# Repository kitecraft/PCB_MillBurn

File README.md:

<div align="center">
  
  <h1>PCB_MillBurn</h1>
  <p>
    <b>Turn your Gerber files into a circuit board.</b><br>
    G-code for the mill. SVG for the laser. One app, one board, no guesswork.
  </p>
  <p>

  </p>
  <p>
    <a href="https://github.com/kitecraft/PCB_MillBurn/releases/latest"><b>Download</b></a> ·
    <a href="#quick-start">Quick start</a> ·
    <a href="#status">What has been proven on metal</a> ·
    <a href="Documentation/README.md">Design docs</a>
  </p>
</div>

---

<sub>A 66-up panel — 11,414 objects, 198 copper islands — with the emitted isolation and cut-out programs drawn back over the copper they were made from.</sub>

---

## What it does

Drop a folder of Gerbers on the window. The board appears. Tell each layer what it should become.
Press Export.

- **Mill it.** Isolation routing, drilling one file per bit, slots and oversized holes routed with an
  end mill, soldermask relief, cut-out with tabs — and, if you like, the copper-clad cut to size first
  so its edges become the datum for everything after.
- **Burn it.** Laser-ready SVG at true 1:1 millimetres, for LightBurn or Inkscape.
- **Or both.** Make the copper with the laser, then drill and cut out on the mill. Same board, same
  origin, same export — and a drill alignment test that lands the holes in the pads.

Every file is one layer. Every file in an export shares one work zero — the board's lower-left
corner, or the stock's. Nothing is written until you have seen a list of exactly what is about to be
written, and every export comes with an HTML page saying what to run, in what order, with which bit.

**It writes files. It does not drive machines.** No serial port, no jogging, no streaming — gSender,
UGS, Candle, LightBurn and LinuxCNC already do that well.

---

## Quick start

1. **Get it.** Download the latest [release](https://github.com/kitecraft/PCB_MillBurn/releases/latest)
   for Windows or Linux, unpack it anywhere, and run `MillBurn` (`MillBurn.exe` on Windows) — the
   folder holds it, `millburn-cli` and the help, nothing else. It is self-contained — you do not
   need .NET installed. (On a fresh Debian or Ubuntu you may need `sudo apt install libfontconfig1`.)
2. **Open a board.** Drag your Gerber export folder onto the window, or `File ▸ Import Gerber
   folder…`. Drill files come along with it. Exporting from KiCad? The
   [export guide](Help/guides/kicad-export.html) lists the settings that work best.
3. **Set the board thickness** in Project info. Everything that cuts through uses it, and it is saved
   with the project. The top of that panel says which folder the Gerbers were read from, in full —
   worth a glance when two of your folders share a name.
4. **Tell each layer what it becomes.** Open a layer row and pick **G-code (mill)**, **SVG
   (laser)**, or **Not exported**. The pill on the collapsed row shows what you chose.
5. **Press Preview** (F5). The programs are drawn back over your board.
6. **Press Export…** (Ctrl+E). Read the list. Choose a folder. Open `YourBoard.project.html` beside
   the files for the run order — and, at its foot, the CLI commands that would write that same
   folder again.

Press **F1** at any point. The help, the questions-and-answers page and the step-by-step guides ship
with the app and work with no network, which is the condition a workshop is usually in.

---

## How to

### Mill a board

| Layer | Set it to | You get |
|---|---|---|
| Top / bottom copper | G-code | Isolation routing around every trace and pad |
| Plated / non-plated holes | G-code | One drilling file per bit, a `.slots.nc` for slots and holes too big to drill, and a page listing them in the suggested order |
| Board outline | G-code | Cut-out with tabs, in depth passes |
| Soldermask | G-code | Mask relief — mills the mask off the pads only |
| *Project info ▸ Build on stock* | — | A `.stock.nc` that cuts the copper-clad to size first; its corner becomes work zero for every file |

Run order on the machine: **stock (if you use it), isolate, drill, cut out.** Between drilling files
you fit the next bit and set Z again on the same spot; X and Y never move.

Per layer you set the tool, cut depth, **isolation width**, break-through past the underside, and tab
count, picking tools from your saved library (`Edit ▸ Tool library…`).

**Tabs go where you want them.** The planner spreads them round the board, one centred on each
straight edge it has room for, the emptiest side first. Each is drawn on the dashed cut path with a
letter — A, B, C — the same letter the Tabs window lists it under. Drag one along the path to move
it, click it to set its own width, right-click to take it away, click the path to add one. Tabs
dropped over each other are refused rather than cut as one gap you did not draw.

**Isolation width is a width, not a lap count.** You say how wide a moat you want around every trace
— 0.4 mm by default — and the app works out how many passes that takes with your bit at your depth,
and shows the sum: *4 passes of 0.127 mm clears 0.450 mm*. One lap of a 30° V-bit separates the nets
and is also a gap you cannot see, cannot solder across without bridging, and can close by handling
the board.

### Burn a board

| Layer | Set it to | You get |
|---|---|---|
| Copper | SVG | The traces, ready to burn as a resist |
| Copper, **inverted** | SVG | Everything inside the board edge *except* the traces — burn the resist *off* a painted board |
| Silkscreen | SVG | Centrelines straight from the strokes, bucketed by whether they fit your beam |
| Soldermask | SVG | The openings, which is exactly what gets lasered |

Every SVG in one export shares **one page origin and size**, so layers land on top of each other in
the laser software without a single alignment step. Bottom-side layers are mirrored for you, and the
export says which way to flip the stock.

### Both machines, one board

Set the copper layers to SVG and the drill and outline layers to G-code, and export once. Same board,
same origin. When the board moves from the laser to the mill, the holes still have to land in pads
that are already there — which is what drill alignment is for.

---

## Drill alignment

<table>
<tr>
<td width="44%" valign="top">

</td>
<td valign="top">

**A 0.8 mm hole in a 1.6 mm pad leaves 0.4 mm of copper either side.** Put work zero 0.3 mm out and
one side of that ring is gone.

`Job ▸ Drill alignment…` writes a test that brings the bit down over a real pad with the spindle
off and stops it a tenth of a millimetre above the copper. Jog the tip to the middle of the hole,
type the two numbers the machine shows, and test again. When it lands dead centre by itself, one
button writes every program you tick again — drilling, slots, the outline — with that correction
built in.

**Measure a second hole** at the far end of the board and the *turn* is corrected too, not just the
shift: a board a quarter of a degree out looks perfect where you measured it and misses by 0.3 mm
across 70 mm. The two holes are also a known distance apart, which is checked against the distance
you just measured — copper-clad does not stretch, so a disagreement means a hole was read wrongly
and nothing is written. If the project cuts its own stock, two holes in the waste give you something
to measure against *before* anything is drilled, from either side of the board.

The photo is the same pads drilled twice: the first holes from the plain files, the second from the
aligned ones, a couple of tests later.

The [drill alignment guide](Help/guides/drill-alignment.html) walks through it. It also ships with
the app, under `Help ▸ Guides`.

</td>
</tr>
</table>

---

## The parts that stop you ruining boards

This is the half that does not show up in a feature list, and it is the half worth having.

**Watch the job in the air first.** Any program can be rewritten to trace the same path 5 mm up with
the spindle never started. It rewrites *the emitted file*, not the toolpath, and re-parses its own
output to prove nothing moving sideways does so below that height. Feeds are kept, so you also find
out it is a ninety-minute job.

**Follow the board that is actually on your table.** Isolation cuts 0.05 mm deep; clamped copper-clad
is 0.1–0.2 mm out of flat. So: generate a `G38.2` probing grid, run it in your sender, feed its log
back in, and every program is bent to the measured surface — degrading to a tilt or an offset when
the measurements cannot justify a surface. One rule comes with it, printed on the probing file
itself: **mark the spot you zero Z on and use it every time.**

**Dial the bit in before you trust it.** `Job ▸ Test cuts…` cuts a few bands on scrap — one per depth,
or one per feed — plus a width ladder, and writes a page explaining how to read them with nothing but
a loupe. Every number the app computes about a cut comes from your tool library; this is how you check
the library is telling the truth.

**Say what to do at the machine.** Every export writes a project page with the run order, and every
drill layer a page listing its files in the suggested order with the bit and hole count for each.
Routing pages name any slot that has no cutter and will not be made.

**Refuse rather than guess.** A dry run that is wrong is worse than none, because it is the thing you
trust just before committing a board. So incremental mode is refused, not guessed at. A levelling
job that runs outside the probed area is refused. A slot too narrow for any cutter you own is refused
by name. Settings that contradict each other are refused rather than quietly clamped.

**Say what changed.** `File ▸ Refresh from source` compares the project against the folder it came
from and shows you what moved before it applies anything.

---

## Optimised toolpaths

A mill spends a surprising share of a job in the air, crossing the board from one cut to the next.
MillBurn plans that part as carefully as the cuts themselves.

<table>
<tr>
<td width="50%" valign="top">

<p><b>pcb2gcode's outline program</b> for the same panel, opened in MillBurn: 2,915 mm of travel.</p>
</td>
<td width="50%" valign="top">

<p><b>MillBurn's</b>, from the same Gerbers: 796 mm with the default settings, the trip back to the corner at the end included.</p>
</td>
</tr>
</table>

<sub>Travel only, drawn from the emitted G-code; the cutting moves are switched off. The two programs cut to different
depths in different passes, so it is the travel that compares, not the cutting.</sub>

- **The order is solved, not inherited.** Cuts are ordered to shorten the travel between them rather than taken in
  the order the Gerber listed them. A closed contour can start at any of its corners, and the corner is chosen as
  part of the same route.
- **Deeper passes stay with their contour.** Each profile is finished to full depth while the tool is standing over
  it, instead of the whole panel being crossed once per depth step.
- **Inside pieces come out before the frame around them**, so nothing is cut loose while the cutter is still
  working next to it.
- **No lift where there is nothing to lift over.** When the next pass starts where the last one ended, in material
  already cut, the tool carries on without going up to safe height and coming back down.

### And then it got better again

<sub><b>v0.2.0 (left)</b> against <b>v0.1.6 (right)</b> — the same board, the same settings, the same
<b>40,276 mm of cutting</b> in both. Only the getting there changed.</sub>

| | v0.1.6 | v0.2.0 |
|---|---:|---:|
| Cutting | 40,276 mm | 40,276 mm |
| Travel | 1,755 mm | **1,688 mm** |
| Plunges | 614 | **556** |

**The plunges are the part worth looking at.** Travel is the number that sounds important, and 67 mm of it is
a few seconds. But every plunge saved is a retract to safe height, a rapid back to a point the tool was already
standing over, and a slow feed down again — on a machine whose Z moves at 100 mm/min, **about 2.7 seconds each**.
Fifty-eight of them is a couple of minutes, on a job where nothing about the cutting changed at all.

That came from the optimizer learning that a channel cut at several depths can be entered from either end, and from
the tool staying down between passes that touch. Neither changes a single cutting move.

pcb2gcode got the whole job working long before this project existed — see [Thanks](#thanks). This is one place
where there was room to do more, and [Documentation/03](Documentation/03-Toolpath-Optimization.md) explains how.

---

## See it

<table>
<tr>
<td width="50%" valign="top">

<p><b>Check the cut before you make it.</b> One layer's copper, one layer's toolpath, everything
else off. The path drawn is parsed back out of the emitted G-code — not from the toolpath that made
it — so what you are looking at is the file the machine will run.</p>
</td>
<td width="50%" valign="top">

<p><b>Nothing is written by surprise.</b> Every file, what it will do, how long it takes, how much
it simplified, and anything worth checking — before a single byte lands on disk.</p>
</td>
</tr>
<tr>
<td width="50%" valign="top">

<p><b>Drilling gets a page of its own.</b> One file per bit, in the suggested order, with the hole
count for each and what you have to set again between them. Written beside the programs, as HTML.
Routed slots get one too.</p>
</td>
<td width="50%" valign="top">

<p><b>The machine's numbers are yours.</b> Safe height, approach, rapid rate, decimals, canned
cycles, dry-run height, probing grid, levelling — or read straight from your controller's GRBL `$`
dump. Checked for contradictions, and refused rather than silently clamped.</p>
</td>
</tr>
</table>

<sub>The actual exported SVG, opened in a browser. Real millimetres, and every kind of geometry on a
colour of its own — the copper to clear in blue, the board outlines in grey, there to place by and
not to burn — so software that sorts an import by colour puts each on its own layer. This artwork
has been laser-engraved onto copper-clad and measured true to within 0.1 mm.</sub>

### It is also just a really good Gerber viewer

Point it at any Gerber export folder and look at your board — fast, correct, and offline.

- **Reads what your EDA tool actually writes.** Gerber RS-274X and X2, aperture macros, negative
  polarity, step-and-repeat, arcs kept as arcs. Excellon drill files including the zero-suppressed
  dialects, G85 slots and routed slots, and drill files written as Gerber.
- **Knows what each file is** from its X2 `.FileFunction` — not from its filename — *says so*
  when it had to guess, and lets you set it by hand when the guess is wrong.
- **Fast.** The viewport holds **98 fps** through a full zoom sweep on 500,247 segments.
- **Opens anybody's G-code too.** `File ▸ Open G-code…`, or drag a `.nc` onto the window. It parses
  the text, so a program from any CAM tool draws the same way.
- **Light and dark**, with layer colours you pick and it remembers.

---

## The CLI

The whole pipeline is scriptable, and it is the same code the window runs. The executable is
`millburn-cli`, beside `MillBurn` in the download; from a source tree, `dotnet run --project
src/MillBurn.Cli --` takes its place. Run it with no arguments for the full list.

```sh
millburn-cli board   <gerber-folder> --png board.png          # detect layers, render headlessly
millburn-cli inspect <folder>                                  # what was understood, and what was not

millburn-cli export  <folder-or-project> --write -o out/       # every layer, one file each
millburn-cli export  <folder> --set F_Cu.gbr=svg- --write      # svg- inverts
millburn-cli export  <folder> --dry-run --write                # + a .dryrun.nc beside each program
millburn-cli export  <folder> --stock 10,10,10,10 --write      # cut the stock to size, 10 mm border
millburn-cli export  <folder> --isolation-width 0.4 --tabs 3   # as the window sets them, per export
millburn-cli export  <folder> --commands > rebuild.sh          # the commands that rebuild that export

millburn-cli testcut depth --tool "30°" --from 0.02 --step 0.02
millburn-cli testcut copper --probe                            # where the copper stops, probed finely
millburn-cli probe   <folder> --spacing 8                      # a G38.2 grid to run and log
millburn-cli export  <folder> --level probe.log --write        # bend every program to the surface
millburn-cli level   anyones.nc --map probe.log                # works on any G-code, not just ours

millburn-cli align   <project> --hole 3 --at 23.74,47.83       # the drill alignment test
millburn-cli align   <project> --hole 3 --at 23.74,47.83 --hole2 11 --at2 40.49,70.77   # and the turn
millburn-cli export  <project> --align 0.12,-0.05 --align-turn 0.3 --align-about 23.62,47.88 --write

millburn-cli project save <folder> -o board.millburn
millburn-cli tools list
```

---

## What it will not do

Deliberate, all of it.

- **Drive your machine.** No serial port, ever. That is a solved problem and not this one.
- **Panelise.** Do it in your EDA tool — [KiKit](https://github.com/yaqwsx/KiKit) for KiCad — and
  this will cut the panel.
- **Compensate for kerf or etch bias.** Kerf depends on power, speed, focus, lens and material, all of
  which live in your laser software beside a calibrated material library. Two tools each applying an
  offset gives you a doubly compensated board that looks wrong in neither.
- **Invent a cutter you do not own.** Slots and oversized holes are routed with end mills from your
  tool library: the one you chose, wherever it fits, otherwise the widest that does. If nothing fits,
  that feature is refused by name while the ones that *can* be cut still are.
- **Guess.** Where the honest answer is "this file does something I cannot safely handle", it says so
  and hands the file back unchanged.

---

## Status

**Version 0.4.0.** Solid enough that its author makes boards with it; young enough that you should
run the dry run first and read the pages beside the files.

<table>
<tr>
<td></td>
<td></td>
</tr>
</table>

<sub>A double-sided board, start to finish, on a sub-$500 mill and a diode laser. Stock cut and its
alignment holes drilled on the mill; both coppers burned through paint on the laser and etched; drilled,
slotted and cut out back on the mill, every file corrected by the two-hole alignment; then the mask
openings and legend burned on the laser, both sides. Every step but the etch came out of one project.</sub>

**Proven on metal:**

- **The laser half.** A 66-up panel exported as front-copper SVG and laser-engraved onto copper-clad:
  traces, pads and outer dimensions true to within the ~0.1 mm the caliper can read, which bounds any
  scale error across 165 mm at **0.061 %**.
- **Isolation and cut-out.** Top copper with a 30° V-bit dialled in by the test cuts, bent to a probed
  height map, then the outline routed out with tabs. No hand-editing at any step, and predicted run
  times landed inside their brackets.
- **Stock, drilling, slots and alignment.** The project's own test board, double-sided, with its copper
  made by the laser: the stock cut to size on the mill, then drilled one file per bit, 1 mm slots and
  2.2–3.5 mm holes routed with an end mill, and every hole lined up on its pad with the drill alignment
  test.
- **Since v0.1.0, on the same board.** Top-copper isolation staying down between touching passes, in
  28:45 against an estimate of 16–46 minutes; the outline cut out with three tabs; and every routed hole
  and slot cut in one continuous descent, both routing files finishing inside their estimates.
- **Since v0.1.1.** Drills and edge cuts run from a two-hole correction, which takes the board's
  *rotation* out as well as its shift — "as good as I can expect", from the machinist who asked for it.
  And tabs now come out the thickness the program promises: the outline cuts one extra pass at the
  tab top, so the tabs are left partial instead of full thickness and the board snaps out.
- **Since v0.1.3.** Routed holes under each of the new short-last-lap choices — kept, spread evenly,
  folded in, and with a finishing lap forced — every hole through and to size, each file's header
  matching the laps it cut, and every run inside its estimate. Pre-cut stock given its two alignment
  holes and nothing else, drilled as 0.8 mm plunges where the program put them. And an SVG placed in
  Falcon by its own centre against an L jig, burned through masking tape onto milled copper: *"as
  best as I can expect."*
- **Since v0.1.4 — the whole mixed workflow, in the photographs above.** 1.6 mm double-sided clad:
  stock cut to size with its two waste holes, painted, both coppers burned on the laser and etched,
  then back to the mill for drilling, slots and the cut-out — **every one of those files corrected by
  the two-hole alignment measured from the waste holes**, which takes out the board's rotation as well
  as a zero set by eye against its edges. Then the soldermask openings and the legend, both sides, on
  the laser. The placing layers in each SVG carried the placement: stock and outline while the board
  was still in its stock, outline alone once it was cut out. *"The mask and silkscreen alignment is
  perfect"*, with the 0.3 mm vias landing inside their pads on a machine whose own errors are
  measured in [09 §1](Documentation/09-Machine-Accuracy-Investigations.md).

- **Since v0.1.5 — the machine itself, measured.** The two machine checks were run on the author's
  mill: backlash under 0.05 mm on both axes, and the two axes square to 0.068°, which is also the
  limit of what pins and calipers can see. Those three readings are what closed a misalignment
  investigation that had looked like a fault in the mill and turned out to be a laser 0.25° out of
  square — written up in
  [Documentation/09](Documentation/09-Machine-Accuracy-Investigations.md).

**Not yet on metal:** milling the soldermask off the pads, milled (rather than lasered) double-sided
isolation, the routed channel between the boards of a panel, and the machine checks *as the app now
writes them* — the readings above came from hand-written prototypes of the same two programs.

985 unit tests and 13 golden-file tests pass with zero warnings under `TreatWarningsAsErrors`, on
every push. Up next is a sprint on **speed and accuracy** rather than features: the pipeline moved
off the UI thread and made cancellable, memoised stages so changing one layer does not redo the
rest, the optimizer's two open items, electrical DRC against the X2 netlist, and reading the
`.gbrjob` every KiCad export already ships. After that, an MCP server over the same libraries, and
solder paste. The full picture, including every bug worth
remembering and what it taught, is in [Documentation/06](Documentation/06-Roadmap-and-Risks.md).

---

## Found a bug?

You will. Please [open an issue](https://github.com/kitecraft/PCB_MillBurn/issues/new/choose) — and
if you can share them, attach **the files**: the Gerber folder zipped, the `.millburn` project, and the
output that came out wrong. A board plus a file is usually enough to reproduce a problem exactly. The
tracker is public, so only attach a board you are happy for anyone to see.

---

## Build it yourself

Requires the **.NET 10 SDK**. Nothing else — no vcpkg, no CMake, no MSYS2.

```sh
dotnet build PCB_MillBurn.slnx
dotnet test  PCB_MillBurn.slnx
dotnet run --project src/MillBurn.App -- <gerber-folder>
```

`Directory.Build.props` sets `TreatWarningsAsErrors`, and CI builds Release on every push — so a
warning is a failed build, which is the point.

### Publishing

Self-contained, so nothing has to be installed on the target, and single-file: each program is one
file with its libraries and the .NET runtime inside it, renamed `MillBurn` and `millburn-cli`. One
script does it, for the release and for a local build alike:

```sh
build/publish.sh win-x64   out/windows
build/publish.sh linux-x64 out/linux
```

It empties the output folder first. The two programs start about 50 ms slower than unbundled ones,
because each unpacks itself as it starts.

**One asymmetry, and it will bite.** Publishing Linux binaries *from Windows* leaves them
non-executable — NTFS has no execute bit — so either `chmod +x MillBurn millburn-cli` after copying
them across, or publish on Linux. Pushing a `v*` tag runs [`release.yml`](.github/workflows/release.yml),
which runs the same script on Linux and attaches both archives to the release.

---

## How it is put together

```
src/
  MillBurn.Core       units, transforms, project model, settings
  MillBurn.Gerber     Gerber RS-274X + X2, Excellon drill and route
  MillBurn.Geometry   Clipper2: tessellation, booleans, offsets, area
  MillBurn.Cam        isolation, drilling, slots, outline, stock, mask and silkscreen generators
  MillBurn.Optimize   travel optimizer, motion time model, simplification, pass linking
  MillBurn.Gcode      mill only: emitter, parser, backplot, dry runs, probing, test cuts, alignment
  MillBurn.Post       mill only: post-processor templates — empty, scheduled
  MillBurn.Align      height maps (probe-log import, TPS) and G-code levelling
  MillBurn.Export     SVG. DXF and PDF are scheduled
  MillBurn.Viewer     scene, level of detail, spatial culling, Skia renderer
  MillBurn.Pipeline   the export planner and companion pages tying it together
  MillBurn.App        Avalonia shell (UI only)
  MillBurn.Cli        headless batch driver
tests/
  MillBurn.Tests        unit and property tests
  MillBurn.GoldenTests  golden-file and determinism regression
  boards/               seven real KiCad exports, committed
Help/                   the offline help, FAQ and guides the app ships with
design/                 KiCad sources of the project's own test board
```

Every algorithm lives in a UI-free `net10.0` library; only `MillBurn.App` references a UI framework.

**Design documentation is in [`Documentation/`](Documentation/README.md)** — why the code is shaped
the way it is, written for whoever maintains it. It is considerably more interesting than a changelog.

| Doc | Subject |
|---|---|
| [01](Documentation/01-Architecture.md) | Solution layout, incremental pipeline, scope boundary, licensing |
| [02](Documentation/02-Gerber-and-Geometry-Pipeline.md) | Gerber X2 parsing, Clipper2 geometry, isolation, drilling, the outline |
| [03](Documentation/03-Toolpath-Optimization.md) | Why pcb2gcode's travel is bad, and the replacement |
| [04](Documentation/04-Machines-Laser-and-Mixed-Workflows.md) | Laser output, the Job model, board re-alignment |
| [05](Documentation/05-Viewer-and-Export.md) | The G-code viewer and the SVG writer |
| [06](Documentation/06-Roadmap-and-Risks.md) | Phases, acceptance metrics, risks, and every bug worth remembering |
| [07](Documentation/07-UI-Framework-Decision.md) | Avalonia vs. WPF vs. MAUI |
| [08](Documentation/08-Requirements-Matrix.md) | Every requirement in the other seven, traced to what exists |

Test fixtures come in two kinds, both committed and both run everywhere: hand-written cases from the
Ucamco specification, and real KiCad board exports in [`tests/boards/`](tests/boards/README.md). The
first prove the parser handles the specification; the second prove it handles what an EDA tool
actually writes, which is where the bugs have been. Set `MILLBURN_BOARDS` to run the suite against a
private board without committing it.

A third kind is **not** committed: pcb2gcode's test data is GPL-3.0, and redistributing it would carry
that licence into this repository. Point `MILLBURN_GERBER_CORPUS` at a checkout of it for 24 more
Gerbers; those cases skip cleanly when it is absent, so a fresh clone and CI stay green.

---

## Thanks

### To pcb2gcode, first and by a distance

**[pcb2gcode](https://github.com/pcb2gcode/pcb2gcode) is the reason this project knows what it is
for.** For the better part of two decades it has been the answer to "how do I mill a PCB at home",
and an enormous number of boards exist because of it — mine among them. It solved the hard,
unglamorous problems first: isolation from real Gerbers, V-bit geometry, break-through, tabs, the
whole shape of the job. Everything here starts from a problem statement that tool worked out and then
proved, in copper, on thousands of benches.

Where this project does something differently, that is a difference of goals and of what is cheap in
2026 — not a criticism of a tool that got there twenty years earlier with far less to build on. The
maintainers gave that away for free, for decades, and asked for nothing. Thank you.

pcb2gcode is GPL-3.0. It was **read for approach and never copied** — not a line of it is in this
repository — because this project is MIT and taking the code would have quietly relicensed everyone
else's work along with it. That constraint is a form of respect, not an evasion: the ideas are
credited here, and the code stays where its authors put it.

### To Universal G-code Sender

**[UGS](https://github.com/winder/Universal-G-Code-Sender)** and its visualizer taught this project
what a G-code viewer owes the person reading it — the decomposition into renderable layers, the honest
time model, the idea that seeing the rapids is what makes a problem obvious. It is also the sender
this project's output is run through. Also GPL-3.0, also read and never copied, also given away free
for years. Thank you.

### To the libraries this is built on

None of this would exist without work other people gave away:

[**Clipper2**](https://github.com/AngusJohnson/Clipper2) (Angus Johnson) — every boolean and every
offset in this project, on exact Int64 coordinates. It is the single most load-bearing dependency here
and it has never once been wrong. ·
[**NetTopologySuite**](https://github.com/NetTopologySuite/NetTopologySuite) — Voronoi, spatial
indexing, validity. ·
[**SkiaSharp**](https://github.com/mono/SkiaSharp) and the Skia team — the viewport draws half a
million segments at 98 fps because of it. ·
[**Avalonia**](https://github.com/AvaloniaUI/Avalonia) — the reason one codebase is a real desktop app
on Windows and Linux with no per-platform branch. Plus
[**AvaloniaEdit**](https://github.com/AvaloniaUI/AvaloniaEdit) and
[**Dock.Avalonia**](https://github.com/wieslawsoltes/Dock). ·
[**MathNet.Numerics**](https://github.com/mathnet/mathnet-numerics) — the SVD behind the height-map
fit. ·
[**CommunityToolkit.Mvvm**](https://github.com/CommunityToolkit/dotnet) ·
[**Scriban**](https://github.com/scriban/scriban) ·
[**xUnit**](https://github.com/xunit/xunit) and [**Verify**](https://github.com/VerifyTests/Verify). ·
And **.NET** itself, which is why the build instructions are three lines long.

### And to the people who made the inputs make sense

**[Ucamco](https://www.ucamco.com/en/gerber)**, for publishing the Gerber specification openly and
keeping it readable — X2's `.FileFunction` is why this app knows what your files *are* instead of
guessing from their names. · **[KiCad](https://www.kicad.org/)**, for being free, excellent, and the
source of every real board in the test suite. · **[KiKit](https://github.com/yaqwsx/KiKit)**, which
panelises so much better than this ever would that panelising is deliberately not here. · Camilo
Sabogal's [**KiCad-Arduino-Boards**](https://github.com/sabogalc/KiCad-Arduino-Boards), two of the
test boards. · And the **gSender**, **Candle**, **LinuxCNC** and **LightBurn** communities, who make the
machines actually run — this app only writes the files.

And to **RAVNIR**, a Nordic music project from Switzerland, for the beat that drove a very high
development cadence.

---

## How this was built

**Claude AI was used extensively in the creation of this application** — architecture, the great
majority of the code, the tests, and this documentation. It was not used as an autocomplete; it was
used as the thing doing the writing, over many long sessions, under direction.

That direction mattered more than it might sound. Every decision about what the app should *do* came
from the person whose mill and laser this was built for, and most of the bugs worth finding were found
the same way: by cutting a board, measuring it, and coming back with the measurement. An AI will
happily produce a G-code file that passes every test and ruins a piece of copper-clad. The corrective
is a real machine, and a person watching it.

So: written with Claude, driven by a human, and checked against metal. Read the code before you trust
it with a spindle — which is good advice whoever wrote it.

---

## Licence

**[MIT](LICENSE).** Use it for anything, including commercially; keep the copyright notice.

Every dependency is permissively licensed as well — MIT, BSD, BSL-1.0, Apache-2.0 — so there is no
copyleft anywhere in the graph and a build can be shipped by anyone, in any product. The full list is
in [THIRD-PARTY-NOTICES.md](THIRD-PARTY-NOTICES.md).

The two GPL-3.0 projects credited above were read for approach and never copied — no line of either is
in this repository. That is a live constraint on how this project is written, not a formality: it is
what keeps this licence honest and everyone else's work unencumbered.

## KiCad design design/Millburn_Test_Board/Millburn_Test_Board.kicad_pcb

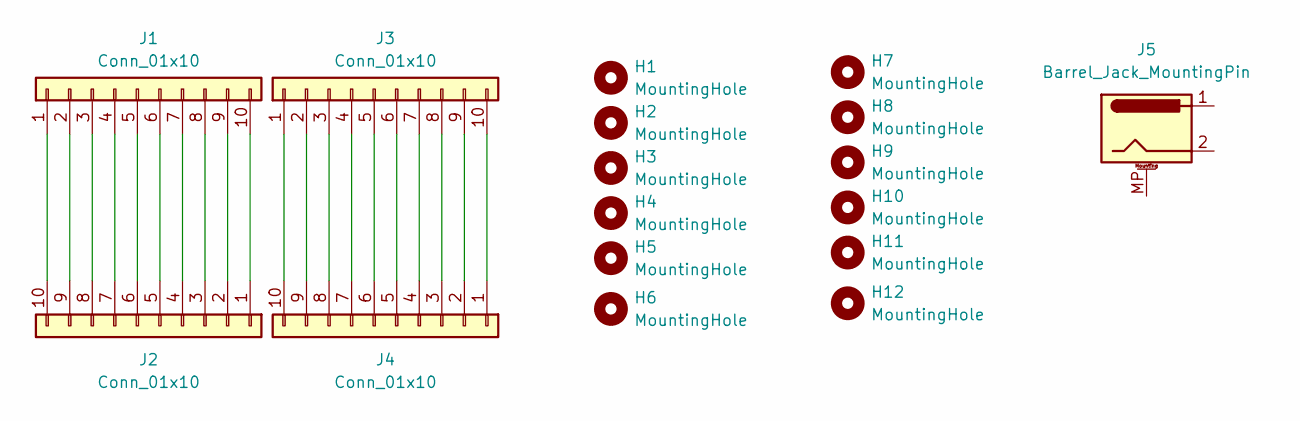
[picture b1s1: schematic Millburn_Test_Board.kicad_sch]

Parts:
H1: MountingHole; MountingHole_2.2mm_M2
H2: MountingHole; MountingHole_2.5mm
H3: MountingHole; MountingHole_2.7mm_M2.5
H4: MountingHole; MountingHole_3mm
H5: MountingHole; MountingHole_3.2mm_M3
H6: MountingHole; MountingHole_3.5mm
H7: MountingHole; MountingHole_2.2mm_M2_Pad_TopBottom
H8: MountingHole; MountingHole_2.5mm_Pad_TopBottom
H9: MountingHole; MountingHole_2.7mm_M2.5_Pad_TopBottom
H10: MountingHole; MountingHole_3mm_Pad_TopBottom
H11: MountingHole; MountingHole_3.2mm_M3_Pad_TopBottom
H12: MountingHole; MountingHole_3.5mm_Pad_TopBottom
J1, J2: Conn_01x10; PinHeader_1x10_P2.54mm_Vertical
J3, J4: Conn_01x10; PinHeader_1x10_P2.54mm_Vertical_SMD_Pin1Left
J5: Barrel_Jack_MountingPin; BarrelJack_GCT_DCJ200-10-A_Horizontal

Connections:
unnamed: J1.1, J2.10
unnamed: J1.2, J2.9
unnamed: J1.3, J2.8
unnamed: J1.4, J2.7
unnamed: J1.5, J2.6
unnamed: J1.6, J2.5
unnamed: J1.7, J2.4
unnamed: J1.8, J2.3
unnamed: J1.9, J2.2
unnamed: J1.10, J2.1
unnamed: J3.1, J4.10
unnamed: J3.2, J4.9
unnamed: J3.3, J4.8
unnamed: J3.4, J4.7
unnamed: J3.5, J4.6
unnamed: J3.6, J4.5
unnamed: J3.7, J4.4
unnamed: J3.8, J4.3
unnamed: J3.9, J4.2
unnamed: J3.10, J4.1

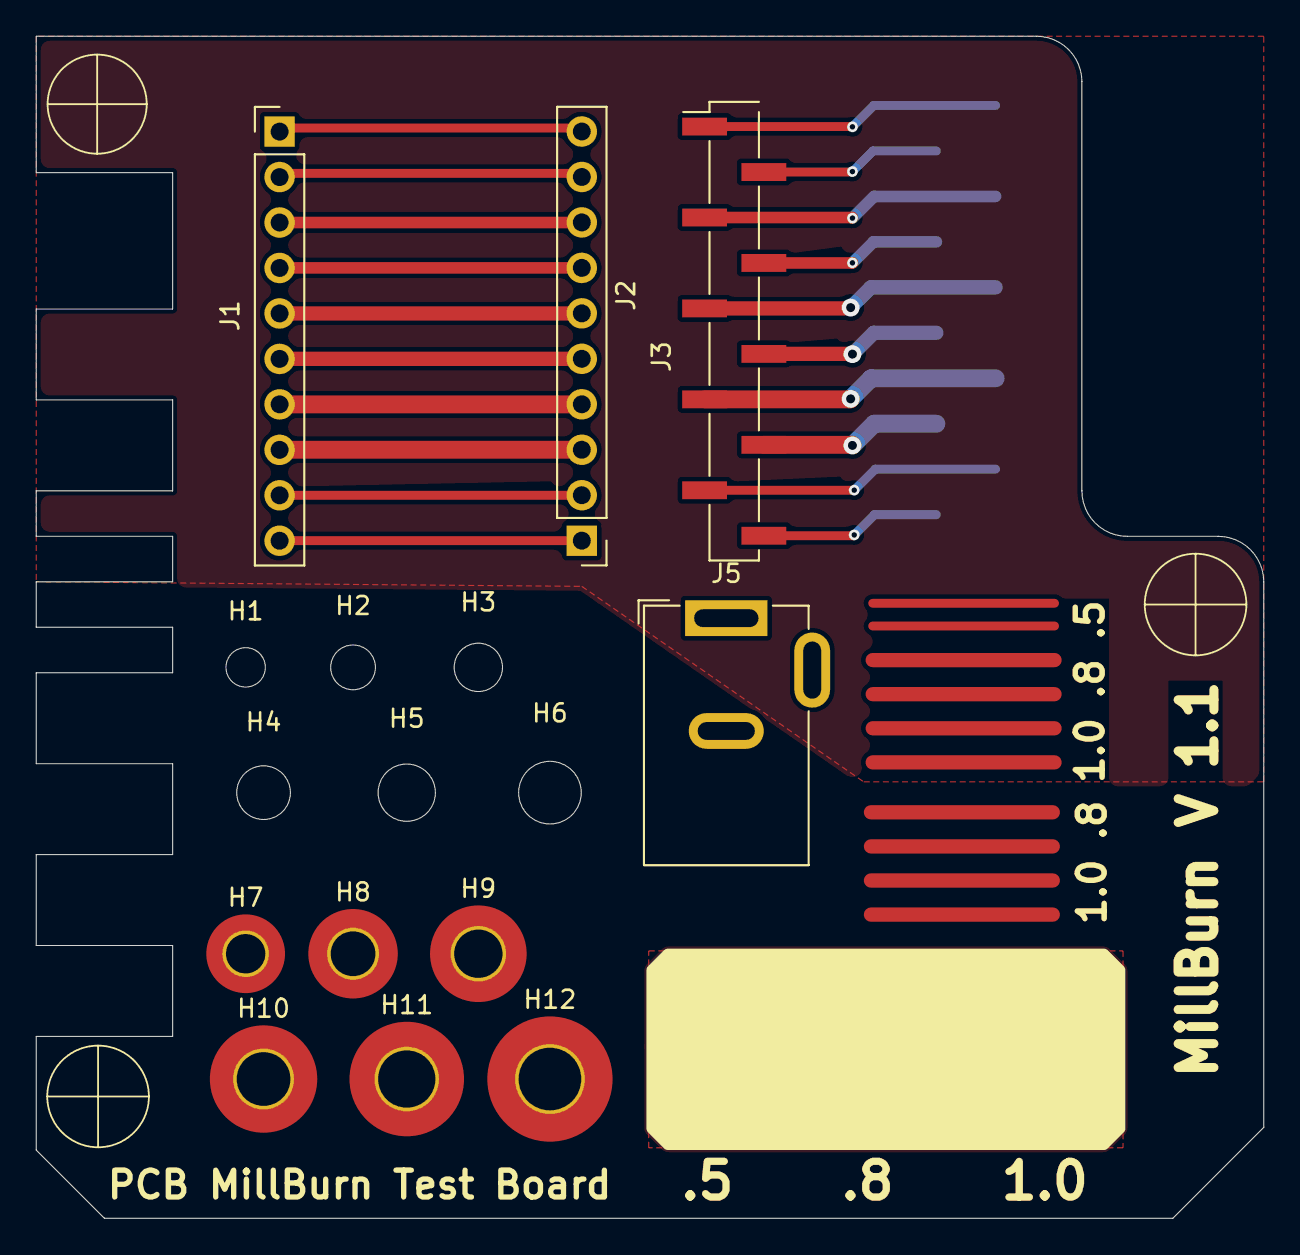
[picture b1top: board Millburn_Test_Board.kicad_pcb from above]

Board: 2 copper layers, 68.6 x 66.0 mm, 17 parts (1 on the bottom side), 20 nets.
